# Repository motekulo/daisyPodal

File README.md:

# Crouds

A guitar pedal that will run patches prototyped on a Daisy Pod. I've started with making it through hole and accessible to build.

[Here's a demo](https://www.youtube.com/watch?v=Z1YsjiImZnQ) of some of the early effects and overall idea.

## Thanks

- For hardware thanks to work on the Dasiy Petal, the Terrarium and the work of  [Keith Shepherd](https://github.com/bkshepherd) 
- Timothy Schoen and other developers (Alex Mitchell, for example) for Plugdata
- Wasted Audio for the [Heavy hvcc compiler](https://wasted-audio.github.io/hvcc/)
- Graham Wakefield and Gregory Taylor for [Generating Sound and Organizing Time](https://cycling74.com/books/go)

## Things to do - v0.3 to 0.4

- J1-8 labels can go on back of board as well
- fix encoder pins (currently the wrong way around)
- fix schematic connection between pins 1 and 2 of TL074
- increase width of board, and bevel corners to fit in enclosure

## Videos

[Version 0.3 with a delay/ looper patch](https://youtu.be/q5X9XX3Vkqw)

[Version 0.3 with a distortion patch](https://youtu.be/5CY0gC0ThXo)

## Roadmap
SMD version as well as through hole.

## About me
I'm a musician/ lecturer - https://researchers.mq.edu.au/en/persons/denis-crowdy, https://codemusic.studio

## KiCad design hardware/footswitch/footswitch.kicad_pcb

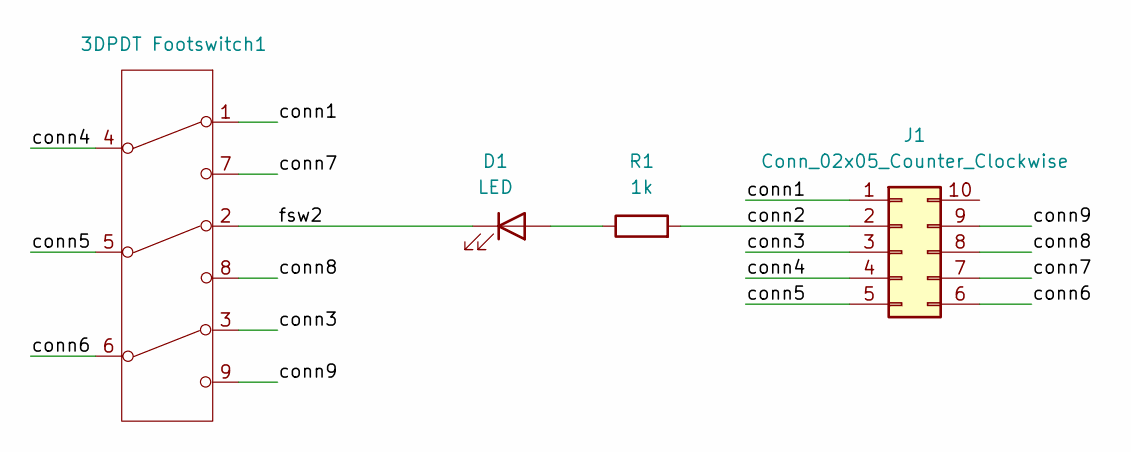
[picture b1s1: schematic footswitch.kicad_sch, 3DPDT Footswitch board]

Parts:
3DPDT Footswitch1: Switches_Stomp_Switch_3PDT
D1: LED; LED_D1.8mm_W3.3mm_H2.4mm
J1: Conn_02x05_Counter_Clockwise; IDC-Header_2x05_P2.54mm_Vertical
R1: 1k; R_Axial_DIN0207_L6.3mm_D2.5mm_P10.16mm_Horizontal

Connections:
/conn1: 3DPDT Footswitch1.1 (A), J1.1
/conn2: J1.2, R1.2
/conn3: 3DPDT Footswitch1.3 (C), J1.3
/conn4: 3DPDT Footswitch1.4 (D), J1.4
/conn5: 3DPDT Footswitch1.5 (E), J1.5
/conn6: 3DPDT Footswitch1.6 (F), J1.6
/conn7: 3DPDT Footswitch1.7 (G), J1.7
/conn8: 3DPDT Footswitch1.8 (G), J1.8
/conn9: 3DPDT Footswitch1.9 (G), J1.9
/fsw2: 3DPDT Footswitch1.2 (B), D1.1 (K)
unnamed: D1.2 (A), R1.1

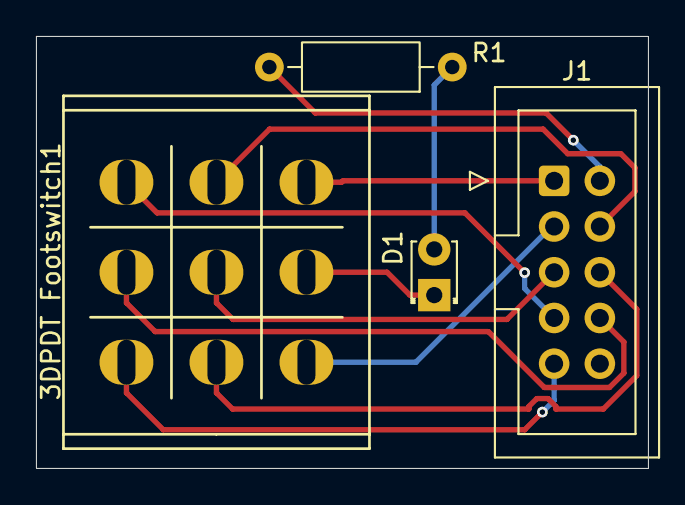
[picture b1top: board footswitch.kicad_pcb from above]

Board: 2 copper layers, 34.0 x 24.0 mm, 4 parts (0 on the bottom side), 11 nets.

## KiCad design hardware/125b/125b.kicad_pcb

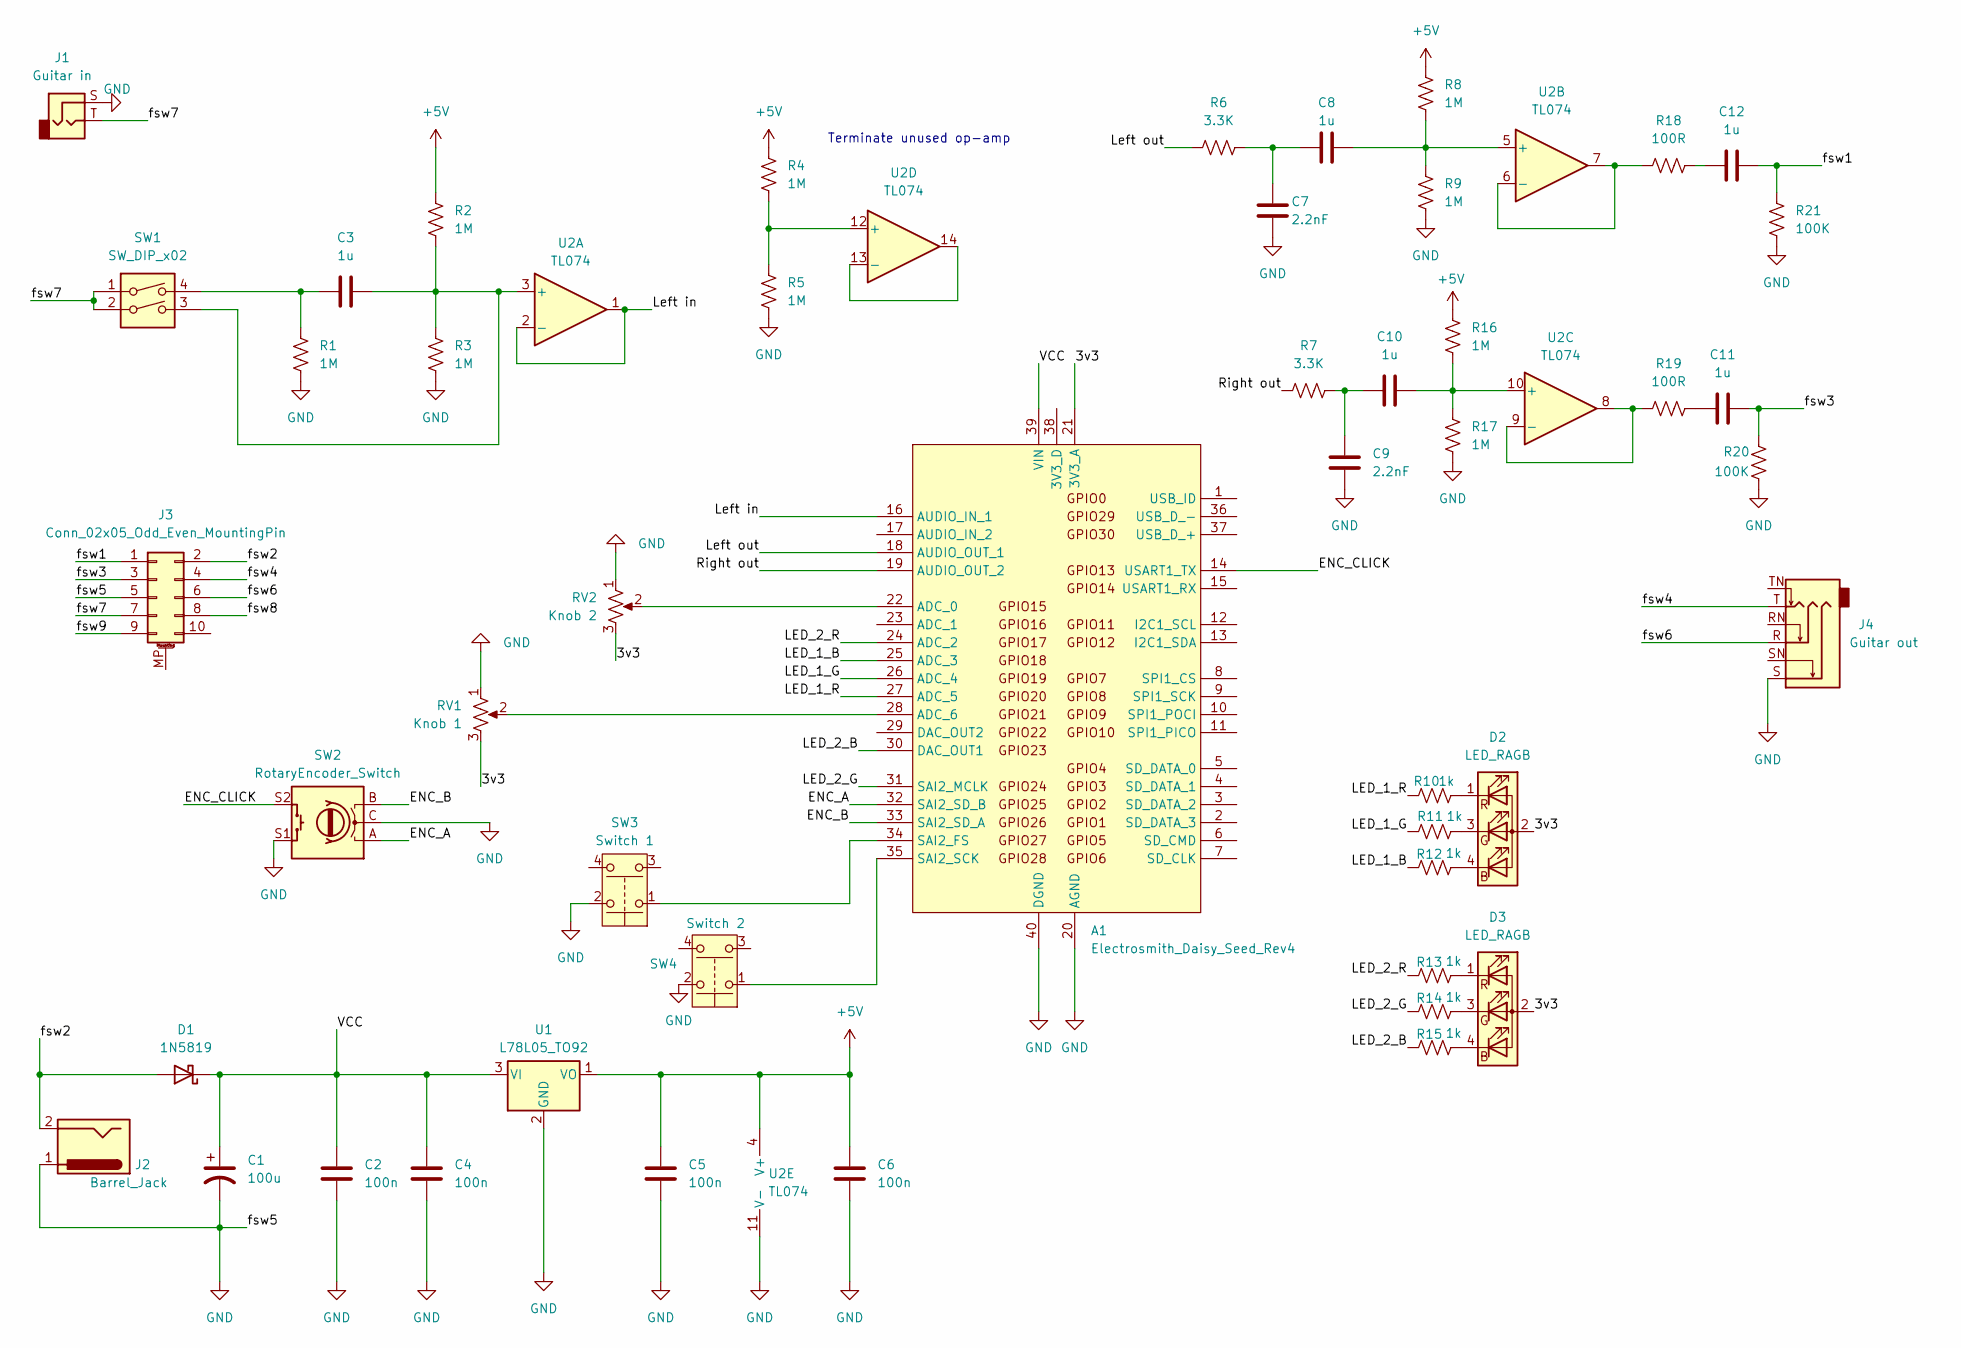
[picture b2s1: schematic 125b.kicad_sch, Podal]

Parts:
A1: Electrosmith_Daisy_Seed_Rev4; Electrosmith_Daisy_Seed
C1: 100u; C_Radial_D5.0mm_H11.0mm_P2.00mm
C2, C4, C5, C6: 100n; C_0805_2012Metric
C3, C8, C10, C11, C12: 1u; C_0805_2012Metric
C7, C9: 2.2nF; C_0805_2012Metric
D1: 1N5819; D_DO-41_SOD81_P7.62mm_Horizontal
D2, D3: LED_RAGB; LED_D5.0mm-4_RGB_Wide_Pins
J1: Guitar in; Jack_6.35mm_Neutrik_NRJ6HF-1-AU_Horizontal
J2: Barrel_Jack; BarrelJack_Horizontal
J3: Conn_02x05_Odd_Even_MountingPin; IDC-Header_2x05_P2.54mm_Vertical
J4: Guitar out; Jack_6.35mm_Neutrik_NRJ6HF-1-AU_Horizontal
R1, R2, R3, R4, R5, R8, R9, R16, R17: 1M; R_0805_2012Metric
R6, R7: 3.3K; R_0805_2012Metric
R10, R11, R12, R13, R14, R15: 1k; R_0805_2012Metric
R18, R19: 100R; R_0805_2012Metric
R20, R21: 100K; R_0805_2012Metric
RV1: Knob 1; Potentiometer_Alps_RK09K_Single_Vertical
RV2: Knob 2; Potentiometer_Alps_RK09K_Single_Vertical
SW1: SW_DIP_x02; SW_DIP_SPSTx02_Slide_9.78x7.26mm_W7.62mm_P2.54mm
SW2: RotaryEncoder_Switch; RotaryEncoder_Alps_EC12E-Switch_Vertical_H20mm
SW3: Switch 1; SolderWire-0.5sqmm_1x02_P4.6mm_D0.9mm_OD2.1mm
SW4: Switch 2; SolderWire-0.5sqmm_1x02_P4.6mm_D0.9mm_OD2.1mm
U1: L78L05_TO92; TO-92_Inline_Wide_78L05_dc
U2: TL074; SOIC-14_3.9x8.7mm_P1.27mm

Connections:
+5V: C5.2, C6.2, R2.1, R4.1, R8.1, R16.1, U1.1 (VO), U2.4 (V+)
/3v3: A1.21 (3V3_A), D2.2 (A), D3.2 (A), RV1.3, RV2.3
/ENC_A: A1.32 (SAI2_SD_B), SW2.A
/ENC_B: A1.33 (SAI2_SD_A), SW2.B
/ENC_CLICK: A1.14 (USART1_TX), SW2.S2
/LED_1_B: A1.25 (ADC_3), R12.1
/LED_1_G: A1.26 (ADC_4), R11.1
/LED_1_R: A1.27 (ADC_5), R10.1
/LED_2_B: A1.30 (DAC_OUT1), R15.1
/LED_2_G: A1.31 (SAI2_MCLK), R14.1
/LED_2_R: A1.24 (ADC_2), R13.1
/Left in: A1.16 (AUDIO_IN_1), U2.1, U2.2 (-)
/Left out: A1.18 (AUDIO_OUT_1), R6.1
/Right out: A1.19 (AUDIO_OUT_2), R7.1
/VCC: A1.39 (VIN), C1.1, C2.2, C4.2, D1.1 (K), U1.3 (VI)
/fsw1: C12.2, J3.1, R21.1
/fsw2: D1.2 (A), J2.2, J3.2
/fsw3: C11.2, J3.3, R20.1
/fsw4: J3.4, J4.T
/fsw6: J3.6, J4.R
/fsw7: J1.T, J3.7, SW1.1, SW1.2
/fsw8: J3.8
/fsw9: J3.9
GND: A1.20 (AGND), A1.40 (DGND), C1.2, C2.1, C4.1, C5.1, C6.1, C7.1, C9.1, J1.S, J2.1, J3.5, J4.S, R1.2, R3.2, R5.2, R9.2, R17.2, R20.2, R21.2, RV1.1, RV2.1, SW2.C, SW2.S1, SW3.2, SW4.2, U1.2 (GND), U2.11 (V-)
unnamed: A1.22 (ADC_0), RV2.2
unnamed: A1.28 (ADC_6), RV1.2
unnamed: A1.34 (SAI2_FS), SW3.1
unnamed: A1.35 (SAI2_SCK), SW4.1
unnamed: C3.1, R1.1, SW1.4
unnamed: C7.2, C8.1, R6.2
unnamed: C9.2, C10.1, R7.2
unnamed: C11.1, R19.2
unnamed: C12.1, R18.2
unnamed: D2.4 (BK), R12.2
unnamed: D2.3 (GK), R11.2
unnamed: D2.1 (RK), R10.2
unnamed: D3.4 (BK), R15.2
unnamed: D3.3 (GK), R14.2
unnamed: D3.1 (RK), R13.2
unnamed: C3.2, R2.2, R3.1, SW1.3, U2.3 (+)
unnamed: C8.2, R8.2, R9.1, U2.5 (+)
unnamed: R18.1, U2.6 (-), U2.7
unnamed: C10.2, R16.2, R17.1, U2.10 (+)
unnamed: R19.1, U2.8, U2.9 (-)
unnamed: R4.2, R5.1, U2.12 (+)
unnamed: U2.13 (-), U2.14

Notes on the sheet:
Terminate unused op-amp

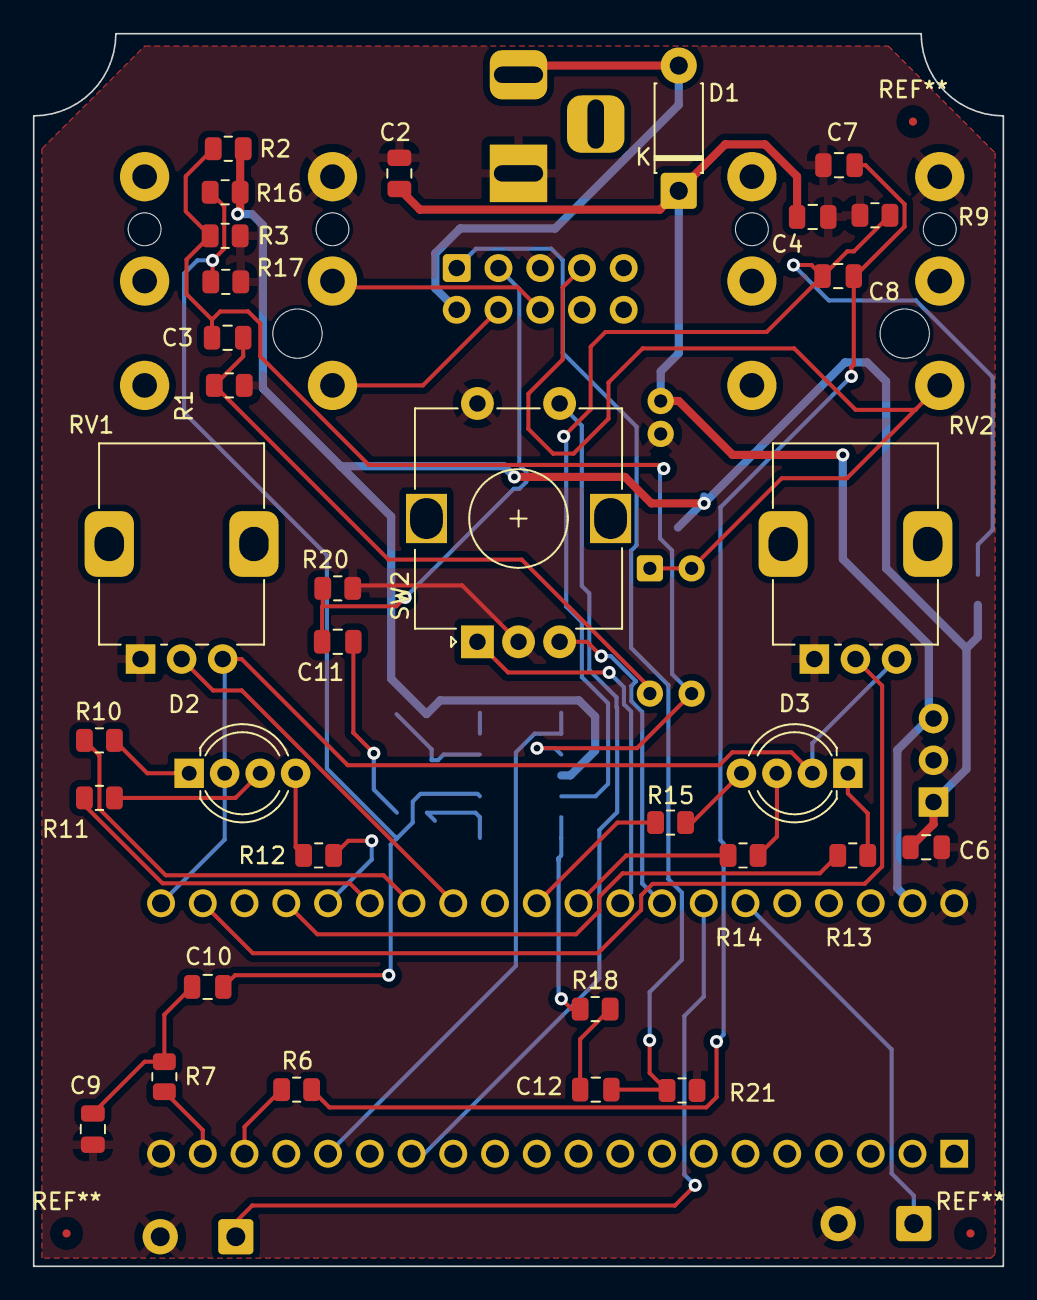
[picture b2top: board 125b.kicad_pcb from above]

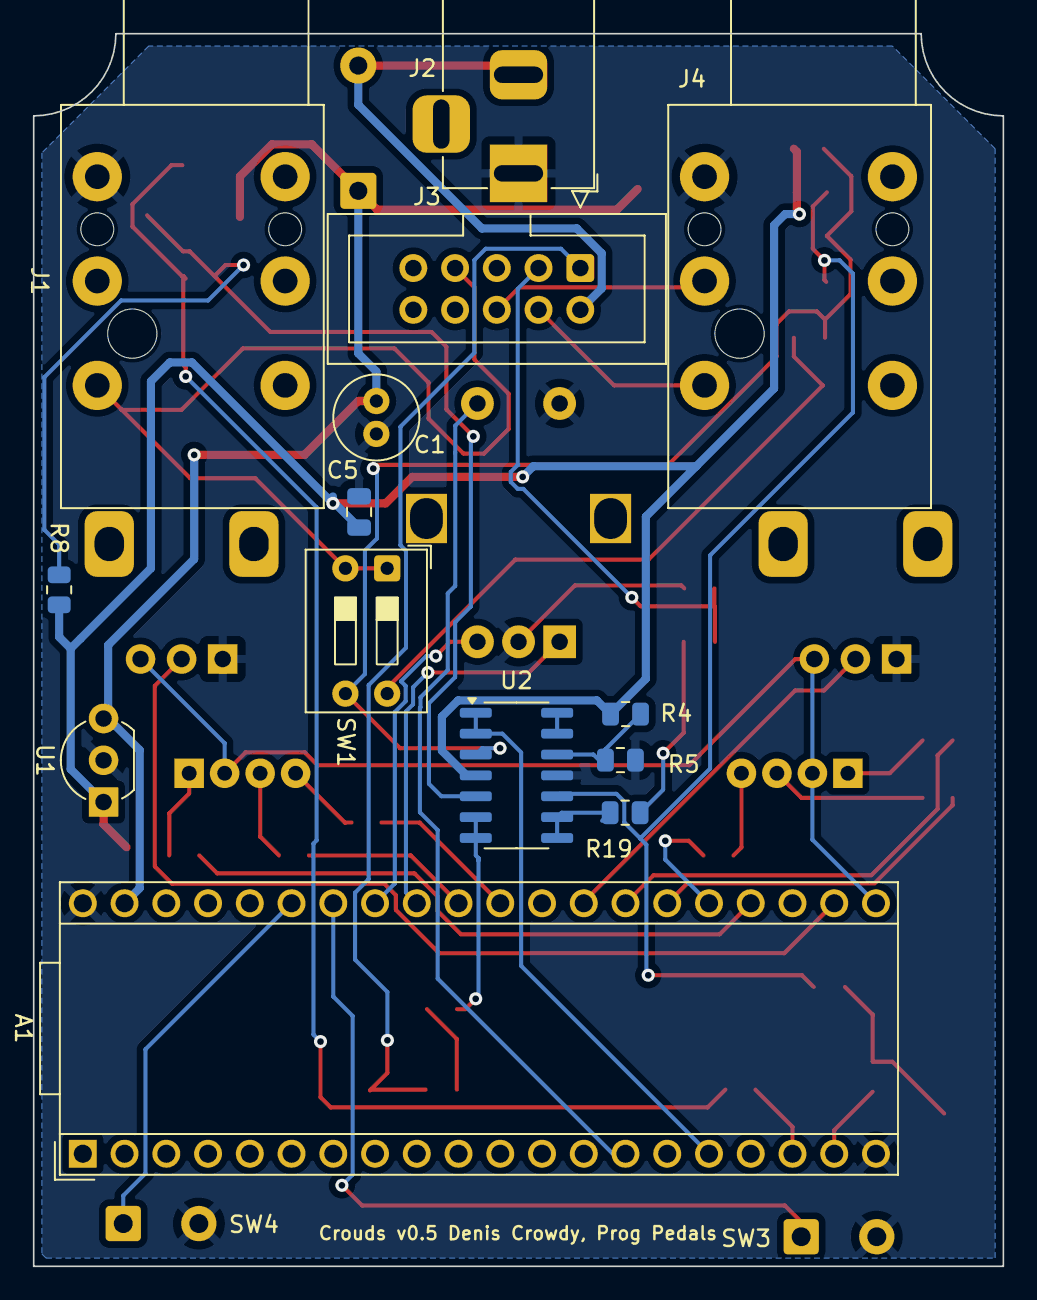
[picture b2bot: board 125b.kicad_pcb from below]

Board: 2 copper layers, 59.0 x 75.0 mm, 49 parts (16 on the bottom side), 44 nets.

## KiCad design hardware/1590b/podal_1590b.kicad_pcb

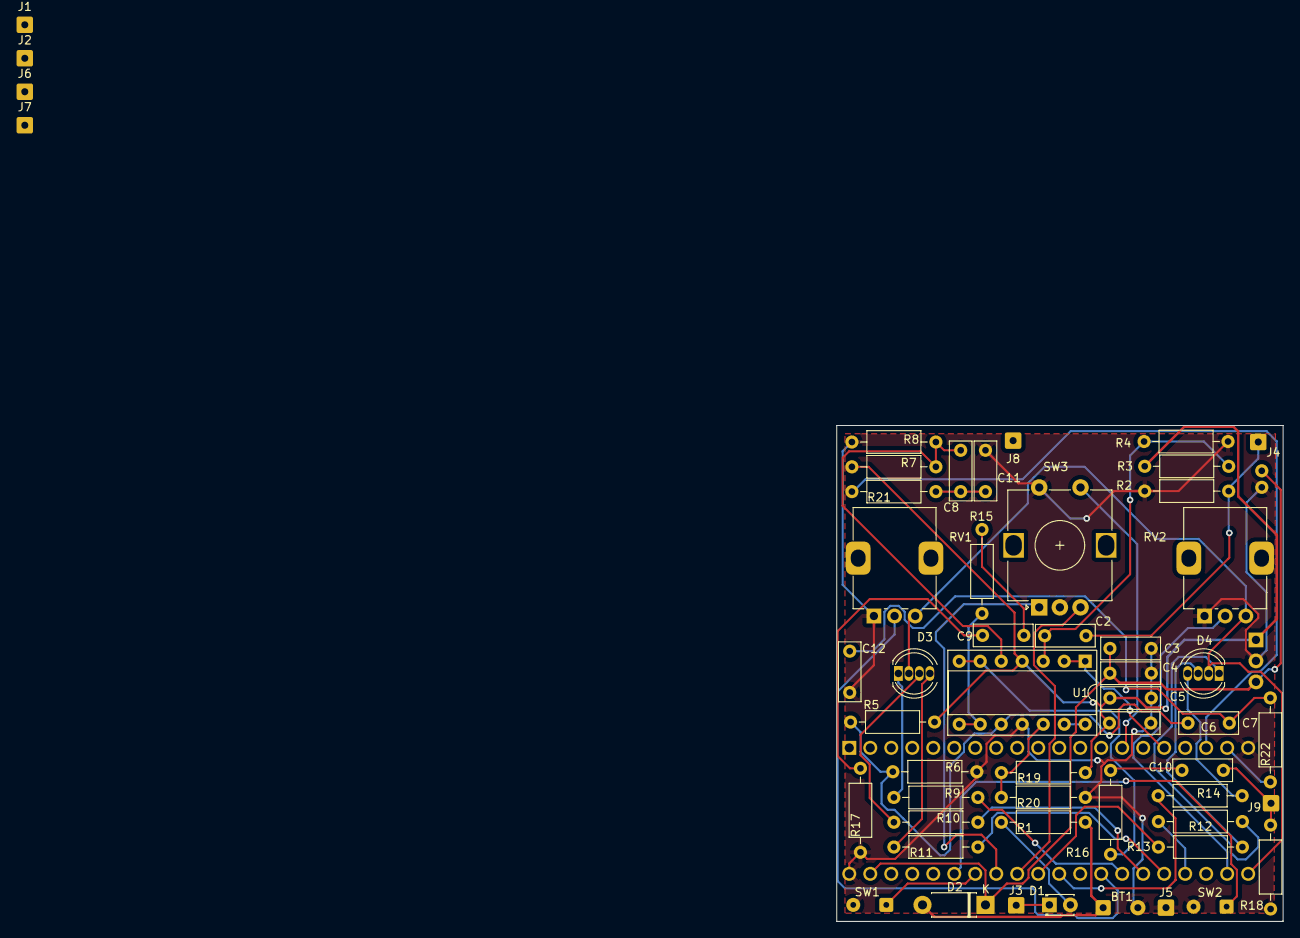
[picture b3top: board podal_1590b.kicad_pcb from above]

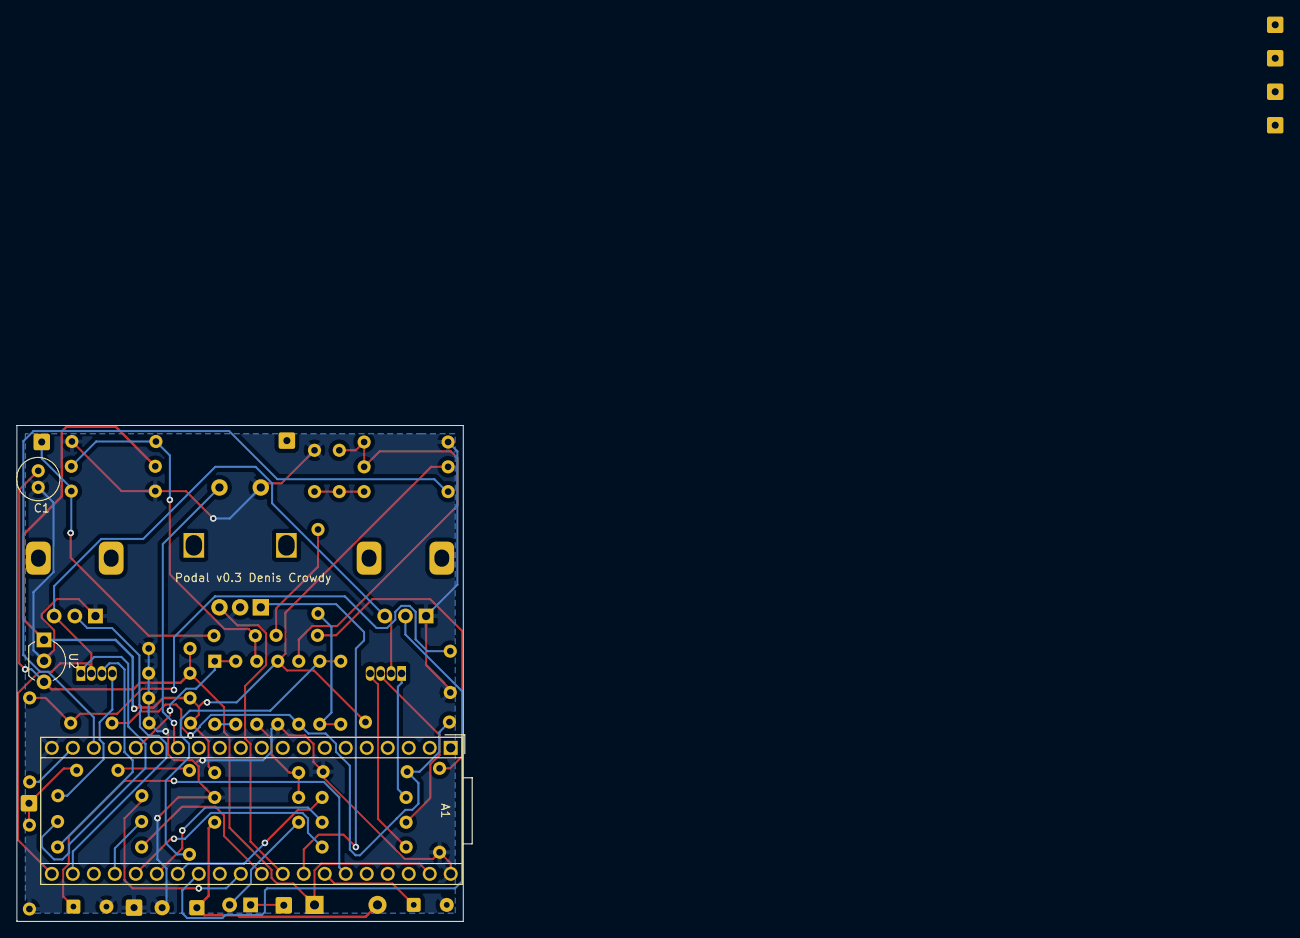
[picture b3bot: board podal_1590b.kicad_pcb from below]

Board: 2 copper layers, 54.0 x 60.0 mm, 56 parts (3 on the bottom side), 43 nets.

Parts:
A1: Electrosmith_Daisy_Seed_Rev4; Electrosmith_Daisy_Seed
BT1: Battery_Cell; SolderWire-0.25sqmm_1x02_P4.2mm_D0.65mm_OD1.7mm
C1: 100u; C_Radial_D5.0mm_H11.0mm_P2.00mm
C2, C7, C8, C9, C10: 1u; C_Rect_L7.0mm_W2.5mm_P5.00mm
C3, C4, C5, C6: 100n; C_Rect_L7.0mm_W2.5mm_P5.00mm
C11, C12: 2.2nF; C_Rect_L7.0mm_W2.5mm_P5.00mm
D1: LED; LED_D1.8mm_W3.3mm_H2.4mm
D2: 1N5819; D_DO-41_SOD81_P7.62mm_Horizontal
D3, D4: LED_RAGB; LED_D5.0mm-4_RGB
J1: Guitar in; SolderWire-0.25sqmm_1x01_D0.65mm_OD2mm
J2: fsw pin 1; SolderWire-0.25sqmm_1x01_D0.65mm_OD2mm
J3: fsw pin 2; SolderWire-0.25sqmm_1x01_D0.65mm_OD2mm
J4: fsw pin 4; SolderWire-0.25sqmm_1x01_D0.65mm_OD2mm
J5: fsw pin 5; SolderWire-0.25sqmm_1x01_D0.65mm_OD2mm
J6: fsw pin 6; SolderWire-0.25sqmm_1x01_D0.65mm_OD2mm
J7: Left out; SolderWire-0.25sqmm_1x01_D0.65mm_OD2mm
J8: Right out; SolderWire-0.25sqmm_1x01_D0.65mm_OD2mm
J9: fsw pin 3; SolderWire-0.25sqmm_1x01_D0.65mm_OD2mm
R1, R9, R10, R11, R12, R13, R14: 1k; R_Axial_DIN0207_L6.3mm_D2.5mm_P10.16mm_Horizontal
R2, R3, R4, R5, R6, R7, R8, R19, R20: 1M; R_Axial_DIN0207_L6.3mm_D2.5mm_P10.16mm_Horizontal
R15, R16: 100R; R_Axial_DIN0207_L6.3mm_D2.5mm_P10.16mm_Horizontal
R17, R18: 100K; R_Axial_DIN0207_L6.3mm_D2.5mm_P10.16mm_Horizontal
R21, R22: 3.3K; R_Axial_DIN0207_L6.3mm_D2.5mm_P10.16mm_Horizontal
RV1: Knob 1; Potentiometer_Alps_RK09K_Single_Vertical
RV2: Knob 2; Potentiometer_Alps_RK09K_Single_Vertical
SW1: Switch 1; SolderWire-0.15sqmm_1x02_P4mm_D0.5mm_OD1.5mm
SW2: Switch 2; SolderWire-0.15sqmm_1x02_P4mm_D0.5mm_OD1.5mm
SW3: RotaryEncoder_Switch; RotaryEncoder_Alps_EC12E-Switch_Vertical_H20mm
U1: TL074; DIP-14_W7.62mm_Socket
U2: L78L05_TO92; TO-92_Inline_Wide_78L05_dc

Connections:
+5V: C5.2, C6.2, R3.1, R5.1, R7.1, R19.1, U1.4 (V+), U2.1 (VO)
/3v3: A1.21 (3V3_A), D3.2 (A), D4.2 (A), RV1.3, RV2.3
/ENC_CLICK: A1.14 (USART1_TX), SW3.S2
/LED_1_B: A1.25 (ADC_3), R11.1
/LED_1_G: A1.26 (ADC_4), R10.1
/LED_1_R: A1.27 (ADC_5), R9.1
/LED_2_B: A1.30 (DAC_OUT1), R14.1
/LED_2_G: A1.31 (SAI2_MCLK), R13.1
/LED_2_R: A1.24 (ADC_2), R12.1
/Left in: A1.16 (AUDIO_IN_1), U1.1, U1.2 (-)
/Left out: A1.18 (AUDIO_OUT_1), R21.1
/Right out: A1.19 (AUDIO_OUT_2), R22.1
/VCC: A1.39 (VIN), C1.1, C3.2, C4.2, D2.1 (K), U2.3 (VI)
GND: A1.20 (AGND), A1.40 (DGND), BT1.2 (-), C1.2, C3.1, C4.1, C5.1, C6.1, C11.1, C12.1, J5.1, R2.2, R4.2, R6.2, R8.2, R17.2, R18.2, R20.2, RV1.1, RV2.1, SW1.2, SW2.2, SW3.C, SW3.S1, U1.11 (V-), U2.2 (GND)
unnamed: A1.22 (ADC_0), RV2.2
unnamed: A1.28 (ADC_6), RV1.2
unnamed: A1.34 (SAI2_FS), SW1.1
unnamed: A1.35 (SAI2_SCK), SW2.1
unnamed: A1.33 (SAI2_SD_A), SW3.A
unnamed: A1.32 (SAI2_SD_B), SW3.B
unnamed: BT1.1 (+), D2.2 (A), R1.1
unnamed: C9.1, R15.2
unnamed: C9.2, R17.1
unnamed: C10.1, R16.2
unnamed: C8.1, C11.2, R21.2
unnamed: C7.1, C12.2, R22.2
unnamed: D1.2 (A), R1.2
unnamed: D1.1 (K), J3.1
unnamed: D3.4 (BK), R11.2
unnamed: D3.3 (GK), R10.2
unnamed: D3.1 (RK), R9.2
unnamed: D4.4 (BK), R14.2
unnamed: D4.3 (GK), R13.2
unnamed: D4.1 (RK), R12.2
unnamed: C2.1, J4.1, R2.1
unnamed: C10.2, J9.1, R18.1
unnamed: C2.2, R3.2, R4.1, U1.3 (+)
unnamed: C8.2, R7.2, R8.1, U1.5 (+)
unnamed: R16.1, U1.6 (-), U1.7
unnamed: C7.2, R5.2, R6.1, U1.10 (+)
unnamed: R15.1, U1.8, U1.9 (-)
unnamed: R19.2, R20.1, U1.12 (+)
unnamed: U1.13 (-), U1.14

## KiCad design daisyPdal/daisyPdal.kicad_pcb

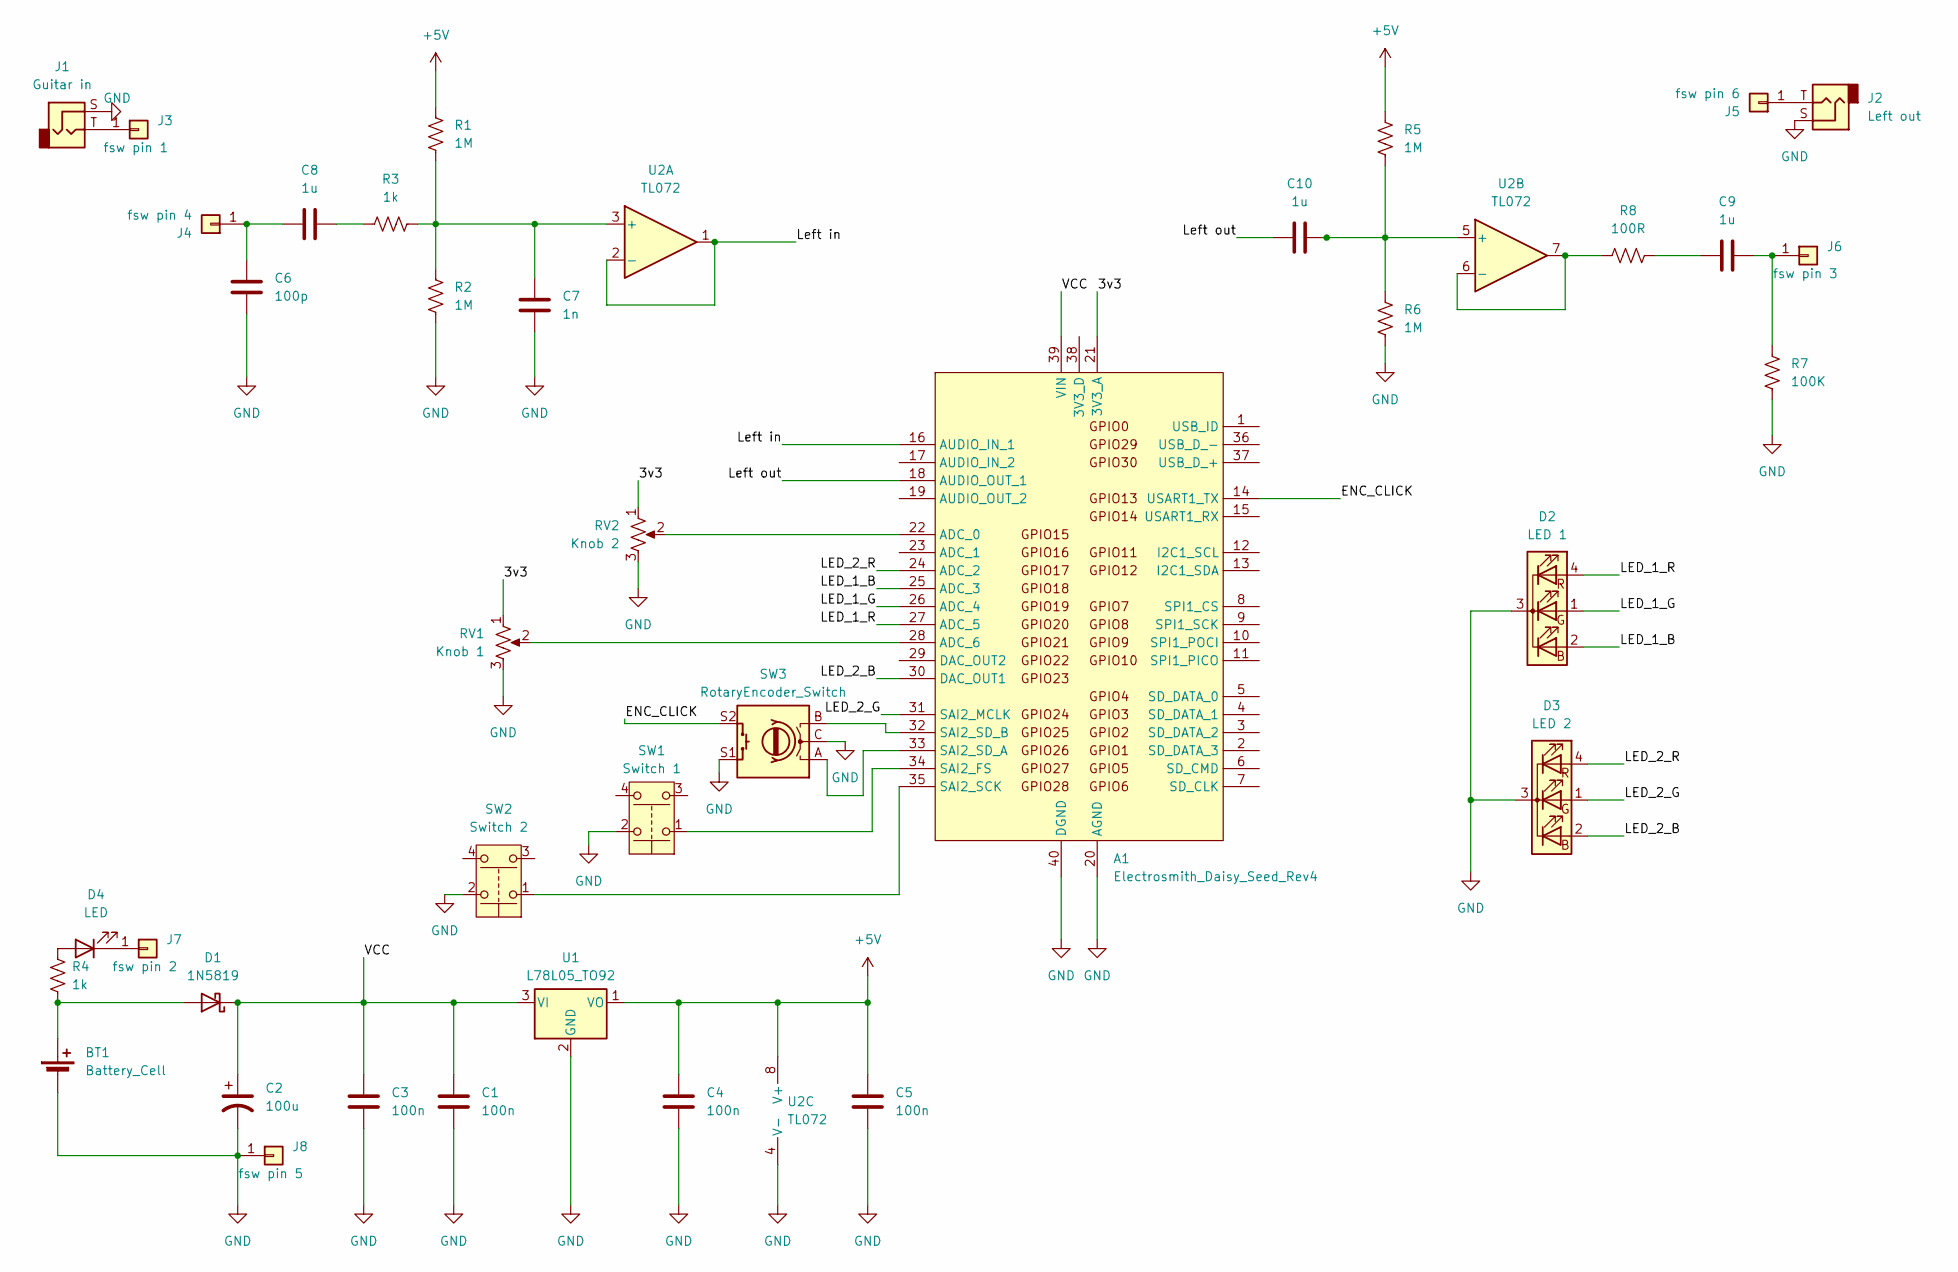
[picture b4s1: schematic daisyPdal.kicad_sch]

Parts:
A1: Electrosmith_Daisy_Seed_Rev4; Electrosmith_Daisy_Seed
BT1: Battery_Cell; BarrelJack_Horizontal
C1, C3, C4, C5: 100n; C_Rect_L9.0mm_W2.5mm_P7.50mm_MKT
C2: 100u; C_Radial_D10.0mm_H16.0mm_P5.00mm
C6: 100p; C_Rect_L9.0mm_W2.5mm_P7.50mm_MKT
C7: 1n; C_Rect_L9.0mm_W2.5mm_P7.50mm_MKT
C8, C9, C10: 1u; C_Rect_L9.0mm_W2.5mm_P7.50mm_MKT
D1: 1N5819; D_DO-41_SOD81_P7.62mm_Horizontal
D2: LED 1; LED_D5.0mm-4_RGB
D3: LED 2; LED_D5.0mm-4_RGB
D4: LED; LED_D1.8mm_W3.3mm_H2.4mm
J1: Guitar in; Jack_6.35mm_Neutrik_NRJ6HM-1_Horizontal
J2: Left out; Jack_6.35mm_Neutrik_NRJ6HM-1_Horizontal
J3: fsw pin 1; SolderWire-0.75sqmm_1x01_D1.25mm_OD3.5mm
J4: fsw pin 4; SolderWire-0.75sqmm_1x01_D1.25mm_OD3.5mm
J5: fsw pin 6; SolderWire-0.75sqmm_1x01_D1.25mm_OD3.5mm
J6: fsw pin 3; SolderWire-0.75sqmm_1x01_D1.25mm_OD3.5mm
J7: fsw pin 2; SolderWire-0.75sqmm_1x01_D1.25mm_OD3.5mm
J8: fsw pin 5; SolderWire-0.75sqmm_1x01_D1.25mm_OD3.5mm
R1, R2, R5, R6: 1M; R_Axial_DIN0207_L6.3mm_D2.5mm_P10.16mm_Horizontal
R3, R4: 1k; R_Axial_DIN0207_L6.3mm_D2.5mm_P10.16mm_Horizontal
R7: 100K; R_Axial_DIN0207_L6.3mm_D2.5mm_P10.16mm_Horizontal
R8: 100R; R_Axial_DIN0207_L6.3mm_D2.5mm_P10.16mm_Horizontal
RV1: Knob 1; Potentiometer_Alps_RK09K_Single_Vertical
RV2: Knob 2; Potentiometer_Alps_RK09K_Single_Vertical
SW1: Switch 1; SW_CW_GPTS203211B_1 podal
SW2: Switch 2; SW_CW_GPTS203211B_1 podal
SW3: RotaryEncoder_Switch; RotaryEncoder_Alps_EC12E-Switch_Vertical_H20mm
U1: L78L05_TO92; TO-92_Inline
U2: TL072; DIP-8_W7.62mm_Socket

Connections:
+5V: C4.2, C5.2, R1.1, R5.1, U1.1 (VO), U2.8 (V+)
/3v3: A1.21 (3V3_A), RV1.1, RV2.1
/ENC_CLICK: A1.14 (USART1_TX), SW3.S2
/LED_1_B: A1.25 (ADC_3), D2.2 (BA)
/LED_1_G: A1.26 (ADC_4), D2.1 (GA)
/LED_1_R: A1.27 (ADC_5), D2.4 (RA)
/LED_2_B: A1.30 (DAC_OUT1), D3.2 (BA)
/LED_2_G: A1.31 (SAI2_MCLK), D3.1 (GA)
/LED_2_R: A1.24 (ADC_2), D3.4 (RA)
/Left in: A1.16 (AUDIO_IN_1), U2.1, U2.2 (-)
/Left out: A1.18 (AUDIO_OUT_1), C10.1
/VCC: A1.39 (VIN), C1.2, C2.1, C3.2, D1.1 (K), U1.3 (VI)
GND: A1.20 (AGND), A1.40 (DGND), BT1.2 (-), C1.1, C2.2, C3.1, C4.1, C5.1, C6.2, C7.2, D2.3 (K), D3.3 (K), J1.S, J2.S, J8.1, R2.2, R6.2, R7.2, RV1.3, RV2.3, SW1.2, SW2.2, SW3.C, SW3.S1, U1.2 (GND), U2.4 (V-)
unnamed: A1.22 (ADC_0), RV2.2
unnamed: A1.28 (ADC_6), RV1.2
unnamed: A1.34 (SAI2_FS), SW1.1
unnamed: A1.35 (SAI2_SCK), SW2.1
unnamed: A1.33 (SAI2_SD_A), SW3.A
unnamed: A1.32 (SAI2_SD_B), SW3.B
unnamed: BT1.1 (+), D1.2 (A), R4.1
unnamed: C8.2, R3.1
unnamed: C9.1, R8.2
unnamed: D4.2 (A), R4.2
unnamed: D4.1 (K), J7.1
unnamed: J1.T, J3.1
unnamed: C6.1, C8.1, J4.1
unnamed: J2.T, J5.1
unnamed: C9.2, J6.1, R7.1
unnamed: C7.1, R1.2, R2.1, R3.2, U2.3 (+)
unnamed: C10.2, R5.2, R6.1, U2.5 (+)
unnamed: R8.1, U2.6 (-), U2.7

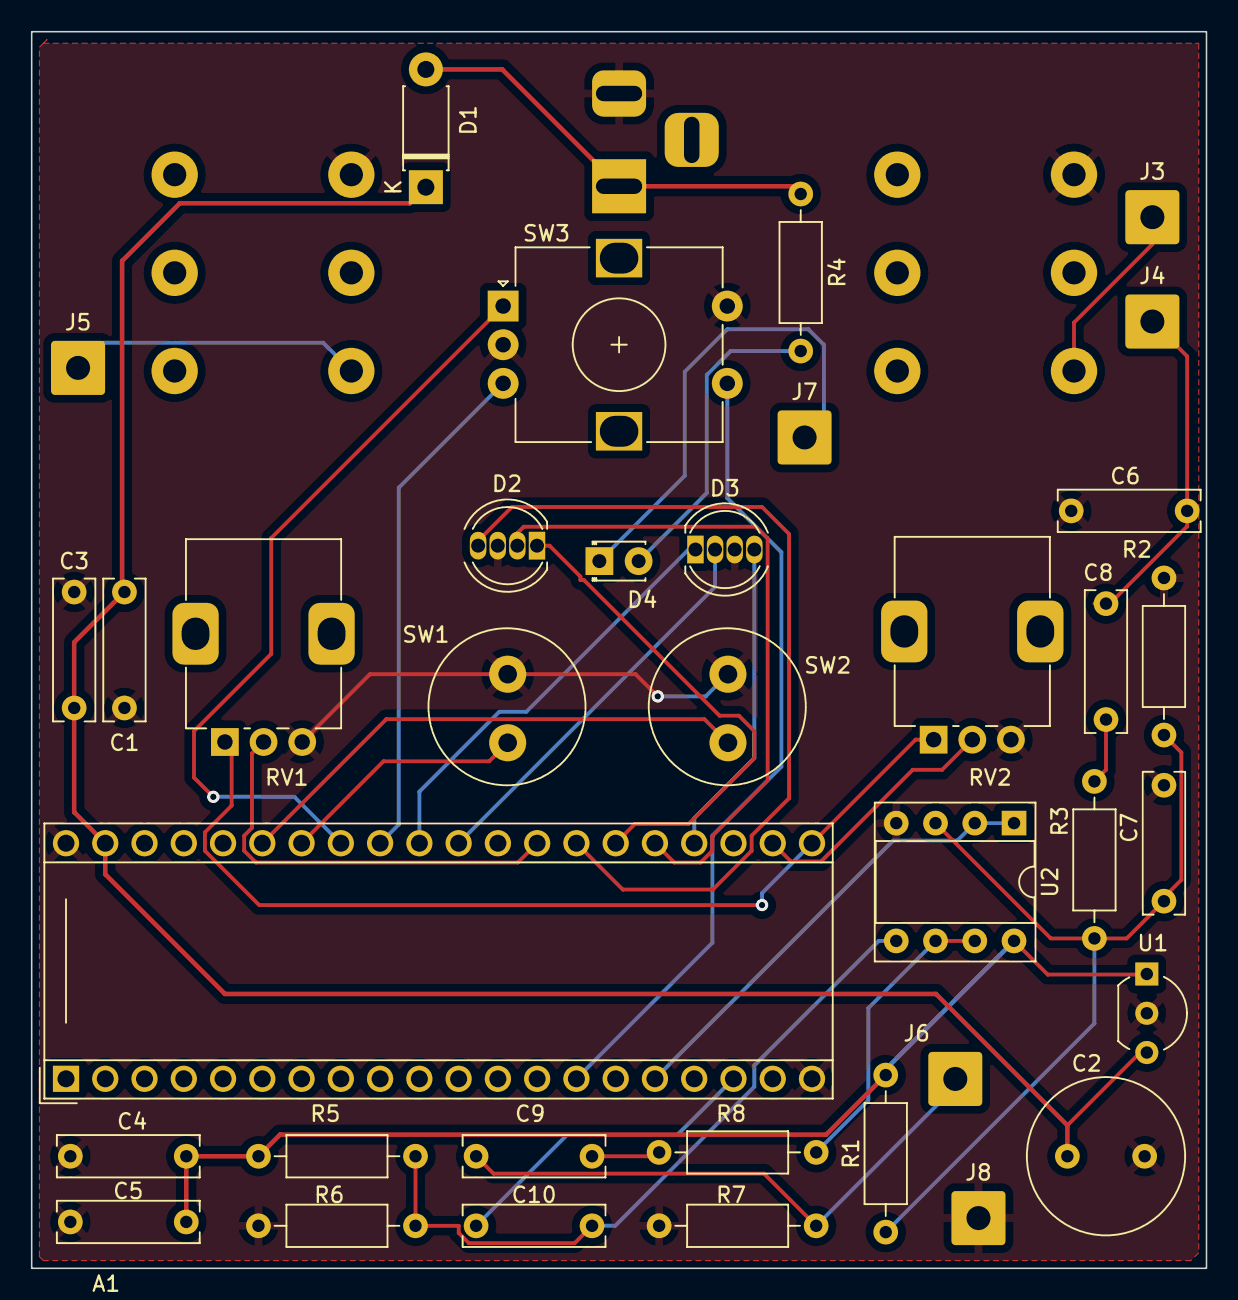
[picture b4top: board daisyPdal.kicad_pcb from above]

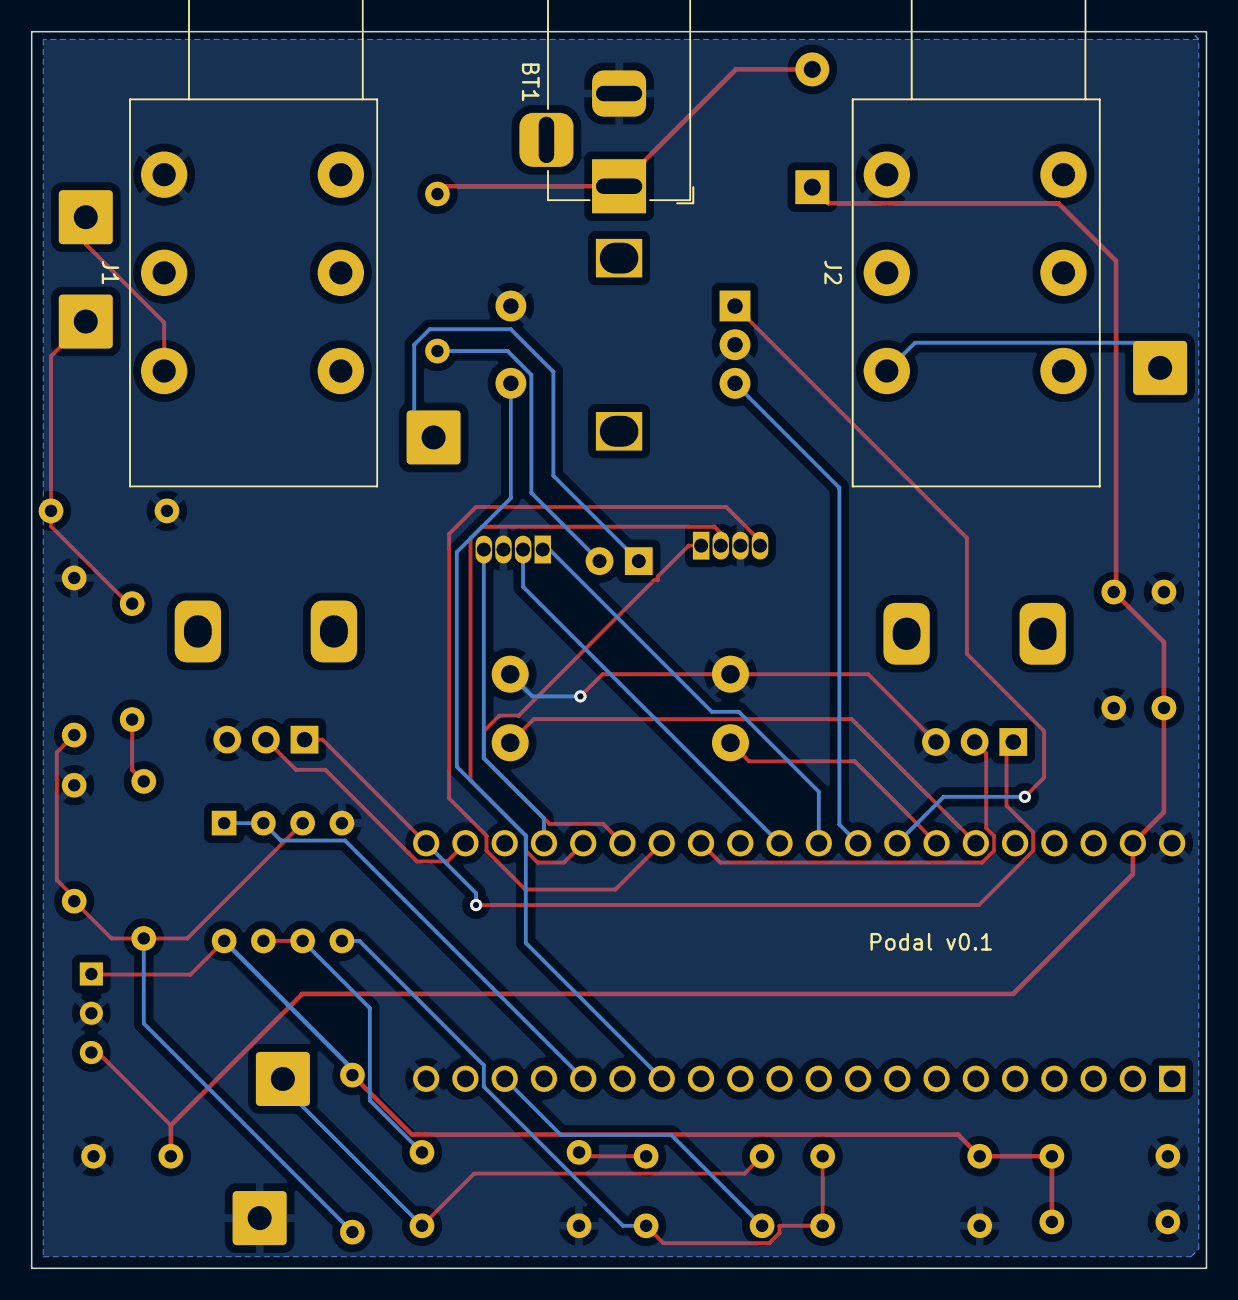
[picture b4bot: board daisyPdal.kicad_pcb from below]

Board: 2 copper layers, 76.0 x 80.0 mm, 39 parts (3 on the bottom side), 31 nets.

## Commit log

2024-02-08 Get a simple test pd patch and knob working
2024-02-11 Start the schematic
2024-02-25 Get the input and output buffers on the schematic
2024-03-05 Update schematic with pots, switches, encoder, LEDs
2024-03-30 Lots of work on the schematic and PCB
2024-03-31 Move pots further apart; separate close traces
2024-03-31 Replace u1 footprint to get correct spacing
2024-04-09 Rename - Podal
2024-04-09 Add simple test delay patch
2024-04-09 Tweaks to README
2024-04-10 Add entry about LEDs to readme
2024-04-23 Add simple delay patch
2024-04-23 Sort out correct RGB LEDS - RAGB
    Common anode on the Pod
2024-04-23 With resistors for the RGB LEDs
2024-04-23 Get the pots the right way around
2024-04-25 Increase hole size of pads for LM7805
2024-04-25 Flip LM7805 to back of board
2024-04-25 Add right out - stereo now
    Replaced TL072 with TL074
2024-04-25 reduce size of box capacitors to fit caps we use
2024-04-25 Place components on PCB in sensible blocks
2024-04-25 Add distortion and filtered delay effects
2024-04-27 Connect everything together on PCB
2024-04-28 Fix input buffer circuit and re-jig PCB
2024-04-30 Terminate unused op-amp
2024-04-30 Add low pass filters at 22kHz on outputs
    Following advice from Daisy forum discussion on Seed rev 7 noise.
    Possible to jumper over these if not desired.
2024-04-30 Tidy up various overlaps
2024-05-01 Tidy labels, print gerbers - mark as v0.2
2024-05-04 Add tremolo patch - mono at this stage
2024-05-04 Remove unnecessary files from repo
2024-05-04 Organise existing effects
2024-05-11 Fix missing connection in schematic on input stage
    Means a jumper needed between pins 1 and 2 of TL074
    on board v0.2
2024-05-12 Update README as we look to v0.3; add changes doc
2024-05-12 Tidy up gen~ overdrive patch
2024-05-12 Get tap tempo delay working with LED indication
2024-05-13 Add multi effects for gen~ and overdrive in Pd
2024-05-13 Tremolo for Pd and plugdata goodness
2024-05-14 Start of a tap tempo delay in Pd
2024-05-14 Trying to get a switch to subdivide the beat
    Not working
2024-05-14 Get subdivision of beat working
    Divide into 2 or 3 (and 1)
2024-05-14 Start of a multi-fx (well 2 anyway) in Pd
    This one has tremolo and delay
2024-05-14 Tidy up multifx patch for Pd
2024-05-14 Add hardware license and rename LICENSE for software
2024-05-14 Tidy up repository
2024-05-14 Remove gen_patches
2024-05-19 Work on a compressor - not patched for Pod yet
    Based on hv.compressor
2024-05-20 Copy files and restart pcb for a 1590b version
2024-05-22 Compressor working with sensible led output
2024-05-25 Start work on connecting traces
2024-05-25 See if we can get some icad compatibility between mac and linux
2024-05-25 Connect everything together
    Board seems messy but good experiment with so many vias?
2024-05-25 Reorganise hardware into enclosure size
2024-05-26 Tidy up pcb and compressor
2024-05-26 Add footprint for the LM7805
2024-05-26 Fix Red and blue LEDs - were the wrong way round
2024-06-04 Adjustments to silkscreen
2024-06-24 Add template to drill enclosure
2024-06-28 Drill template for 125b enclosure
2024-06-28 First go at template for 1590b enclosure
2024-07-07 First attempt at a simple looper
2024-07-07 Tidy up looper and get reset working
2024-07-14 Adjust placement and size of power socket
    1590b
    Some changes to the looper too
2024-07-16 Add template for usb and Daisy access
2025-04-27 Improved overdrive - hpf before drive
    Also adjusted drive factor and cleaned up patch
2025-05-26 The looper with random delay lines
2025-06-01 Copy 1590b version across to start on 125b version
    Heading towards 0.4
2025-06-07 Add switch for line input toggle and fix stereo out
    Bypass will be different for stereo out
2025-06-08 Tidy up scehmatic - grid snapping
2025-06-08 Update PCB and resize for 125b
2025-06-08 Add crouds 2 - random feedback with filter
2025-06-09 Tidy up schematic
2025-06-09 Footprints for audio and power sockets added
    Also DIP switch for line/ guitar input. Ready to start
    moving components around.
2025-06-09 Swap encoder pins
2025-06-09 Components replaced on board after rejig
    Back with the audio and power sockets on board
2025-06-12 Fix unconnected items and update footprints
2025-06-12 Cut out corners for 125b enclosure
2025-06-12 Flip wire connectors to back of board
    Various adjustments of labels and fix overlapping footprints
2025-06-12 Tidied up tracks
2025-06-13 Final minor tweaks then export as 0.4
    Off to fabrication
2025-06-13 rename drill template for 125b
2025-06-14 Update readme with videos
2025-06-14 Tidy video format
2025-06-26 Edits to 125b enclosure drill template
2025-06-26 Add 3d models of Daisy, pots, encoder and audio socket
2025-07-10 add a 3DPDT footswitch to kicad and then schematic
2025-07-10 Add a symbol for a guitar pedal 3dpdt footswitch
2025-07-14 Add schematic and pcb files for footswitch board
2025-07-14 Add stomp box footprint
    From https://github.com/David-Estevez/kicad-library/wiki
2025-07-14 New project for the footswitch board
2025-07-14 Connect up footswitch to IDC 2 x 5
2025-07-14 Wider traces for footswitch PCB and connect main board
2025-07-30 Start work on SMD caps and resistors
2025-07-30 Increase size of holes for switch connectors
2025-07-31 Update 3d models and adjust footprints for local project lib
2025-08-01 Tidy up position of SMD components
2025-08-02 Increase RGB LED footprint for easier soldering
    Also re-adjustLEDs, pots and encoder for symmetry
2025-08-03 Try pin sockets for the footswitch connector
    Can just solder some ribbon wire for this version
2025-08-03 Add GND plane zones
2025-08-03 Everything connected together
2025-08-11 Update README.md
    Calling it Crouds
2025-08-13 Set up power nets to have wider traces
2025-08-13 Add bypass LED and resistor to footswitch board
2025-08-14 Resize footswitch board, adjust footprints
    Resistor and diode added
2025-08-14 Connect everything with traces
    Corrected schematic with fsw2
2025-08-14 All components connected with new IDC socket pos
2025-08-14 Move r8 from underneath audio socket
2025-08-14 Rotate IDC socket for cleaner ribbon direction
2025-08-14 Minor adjustments to footswitch pcb
2025-08-14 Adjust switch connector positions and add fiducials
2025-08-23 Fix stereo on tremolo and subdivision on tap tempo
2025-08-24 Fix up various aspects of tap tempo delay
